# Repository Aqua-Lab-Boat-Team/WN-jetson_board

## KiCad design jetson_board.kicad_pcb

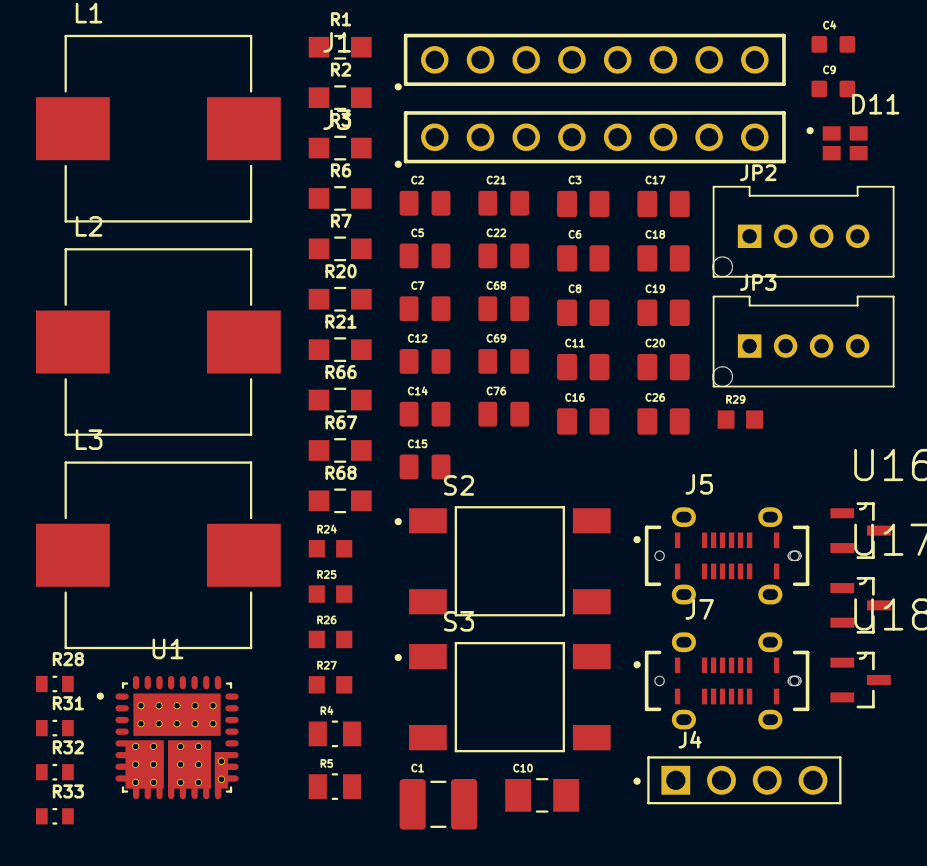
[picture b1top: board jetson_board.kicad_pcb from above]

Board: 2 copper layers, 63 parts (0 on the bottom side), 41 nets, no tracks yet.

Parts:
C1: 10µF 100V; CAPC3225X280N
C2: 0.1µF 100V; CAPC2012X135N
C3, C16, C17, C18, C19: 1µF 100V; CAPC2012X145N
C4, C9: 10nF; CAPC1608X90N
C5, C7: 0.1µF, 25V; CAPC2012X95N
C6, C8: 10µF, 25V; CAPC2012X145N
C10: 47µF; CAPC3216X180N
C11: 10µF; CAPC2012X145N
C12: 0.1µF; CAPC2012X95N
C14, C15: 0.1uF 100V; CAPC2012X135N
C20, C26: 1µ, 100V; CAPC2012X145N
C21, C22: 0.1µ, 25V; CAPC2012X95N
C68, C69, C76: 0.1uF 25V; CAPC2012X95N
D11: CLMVC-FKA-CL1D1L71BB7C3C3; LED_CLMVC-FKA-CL1D1L71BB7C3C3
J1, J3: 6130XX11821_61300811821; 61300811821
J4: PPTC041LFBN-RC; SULLINS_PPTC041LFBN-RC
J5, J7: USB4120-03-C_REVA6; GCT_USB4120-03-C_REVA6
JP2, JP3: B04B-PASK-1
L1, L2, L3: 6.8µH, 8A; IND_PA4342.682NLT
R1, R2, R3: 300k; RES_ERA6AEB304V
R4, R5: 2Ω; RESC2012X65N
R6, R7: 10k; RES_ERA6AEB103V
R20, R21: 100k; RES_ERA6AEB104V
R24, R25, R26, R27: 5.1K; RESC1508X55N
R28: 1.5K 1%; RES_ERJ3EKF1501V
R29: ERA-3AEB4990V; RESC1608X55N
R31, R32, R33: 100 Ohm; RES_ERJ3EKF1000V
R66, R67, R68: 10K; RES_ERA6AEB103V
S2, S3: TS04-66-50-BK-160-SMT-TR; SW_TS04-66-50-BK-160-SMT-TR
U1: MIC28514T-E_PHA; CONV_MIC28514T-E_PHA
U16, U17, U18: BSS123-7-F; SOT95P240X110-3N

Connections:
+3V3: C20.1, C26.1, D11.1, JP2.2, JP3.2, R20.1, R21.1
+5V: J1.4, J1.8, J3.4, J3.8, J4.1
+12V: C9.2, C10.2, C11.2, C12.2, L1.2, R7.2
+VBAT: C1.2, C2.2, R1.1, R3.1, R4.2, U1.5 (PVIN), U1.6 (PVIN), U1.7 (PVIN), U1.8 (PVIN), U1.9 (PVIN), U1.10 (PVIN), U1.11 (PVIN), U1.34 (PVIN), U1.34_1 (PVIN), U1.34_2 (PVIN), U1.34_3 (PVIN), U1.34_4 (PVIN), U1.34_5 (PVIN), U1.34_6 (PVIN)
/BUT_1: C21.1, R20.2, S2.1, S2.3
/BUT_2: C22.1, R21.2, S3.1, S3.3
/COM_D+: J7.A6 (D1+), J7.B6 (D2+)
/COM_D-: J7.A7 (D1-), J7.B7 (D2-)
/I2C1_SCL: JP2.4, JP3.4
/I2C1_SDA: JP2.3, JP3.3
/JETSON_D+: J4.2, J5.A6 (D1+), J5.B6 (D2+)
/JETSON_D-: J4.3, J5.A7 (D1-), J5.B7 (D2-)
/RGB_B: C68.1, R67.2, U16.1 (G)
/RGB_G: C69.1, R66.2, U17.1 (G)
/RGB_R: C76.1, R68.2, U18.1 (G)
/V_USB_BREAKOUT: C17.2, L2.2
/V_USB_COMM: C19.2, L3.2
GND: C1.1, C2.1, C3.1, C5.1, C6.1, C10.1, C11.1, C12.1, C16.1, C17.1, C18.1, C19.1, C20.2, C21.2, C22.2, C26.2, C68.2, C69.2, C76.2, J1.1, J1.5, J3.1, J3.5, J4.4, J5.A1 (GND_A), J5.A12 (GND_A), J5.B1 (GND_B), J5.B12 (GND_B), J5.S1 (SHIELD), J5.S2 (SHIELD), J5.S3 (SHIELD), J5.S4 (SHIELD), J7.A1 (GND_A), J7.A12 (GND_A), J7.B1 (GND_B), J7.B12 (GND_B), J7.S1 (SHIELD), J7.S2 (SHIELD), J7.S3 (SHIELD), J7.S4 (SHIELD), JP2.1, JP3.1, R24.1, R25.1, R26.1, R27.1, R66.1, R67.1, R68.1, S2.2, S2.4, S3.2, S3.4, U1.2 (PGND), U1.16 (PGND), U1.17 (PGND), U1.18 (PGND), U1.19 (PGND), U1.22 (PGND), U1.23 (EXTVDD), U1.29 (PGND), U1.33 (PGND), U1.33_1 (PGND), U1.33_2 (PGND), U1.33_3 (PGND), U1.33_4 (PGND), U1.33_5 (PGND), U1.33_6 (PGND), U1.33_7 (PGND), U1.33_8 (PGND), U1.33_9 (PGND), U1.33_10 (PGND), U1.36 (PGND), U1.36_1 (PGND), U1.36_2 (PGND), U16.2 (S), U17.2 (S), U18.2 (S)
GNDA: C4.1, C7.1, C8.1, R2.2, R29.1, U1.28 (AGND)
unnamed: C14.2, L1.1, R6.2, R28.2, U1.3 (SW), U1.12 (SW), U1.13 (SW), U1.14 (SW), U1.15 (SW), U1.20 (SW), U1.35 (SW), U1.35_1 (SW), U1.35_2 (SW), U1.35_3 (SW), U1.35_4 (SW), U1.35_5 (SW), U1.35_6 (SW)
unnamed: C15.1, R6.1
unnamed: D11.2, R31.2
unnamed: D11.3, R32.2
unnamed: D11.4, R33.2
unnamed: J5.A5 (CC1), R24.2
unnamed: J5.B5 (CC2), R25.2
unnamed: J7.A5 (CC1), R26.2
unnamed: J7.B5 (CC2), R27.2
unnamed: C14.1, U1.4 (BST)
unnamed: R3.2, U1.24 (EN)
unnamed: C9.1, C15.2, R7.1, R29.2, U1.27 (FB)
unnamed: R1.2, R2.1, U1.25 (FREQ)
unnamed: R28.1, U1.1 (ILIM)
unnamed: C5.2, C6.2, R5.2, U1.21 (PVDD)
unnamed: C4.2, U1.26 (SS)
unnamed: C3.2, R4.1, U1.31 (SVIN)
unnamed: C7.2, C8.2, R5.1, U1.30 (VDD)
unnamed: R31.1, U16.3 (D)
unnamed: R32.1, U17.3 (D)
unnamed: R33.1, U18.3 (D)
VBUS_A: C16.2, C18.2, J5.A4 (VBUS_A), J5.A9 (VBUS_A), J5.B4 (VBUS_B), J5.B9 (VBUS_B), J7.A4 (VBUS_A), J7.A9 (VBUS_A), J7.B4 (VBUS_B), J7.B9 (VBUS_B), L2.1, L3.1
